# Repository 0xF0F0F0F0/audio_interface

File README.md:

# WM8731 audio_interface

KiCad project files for a stereo audio interface running at 24-bits/96kHz using the WM8731 codec.

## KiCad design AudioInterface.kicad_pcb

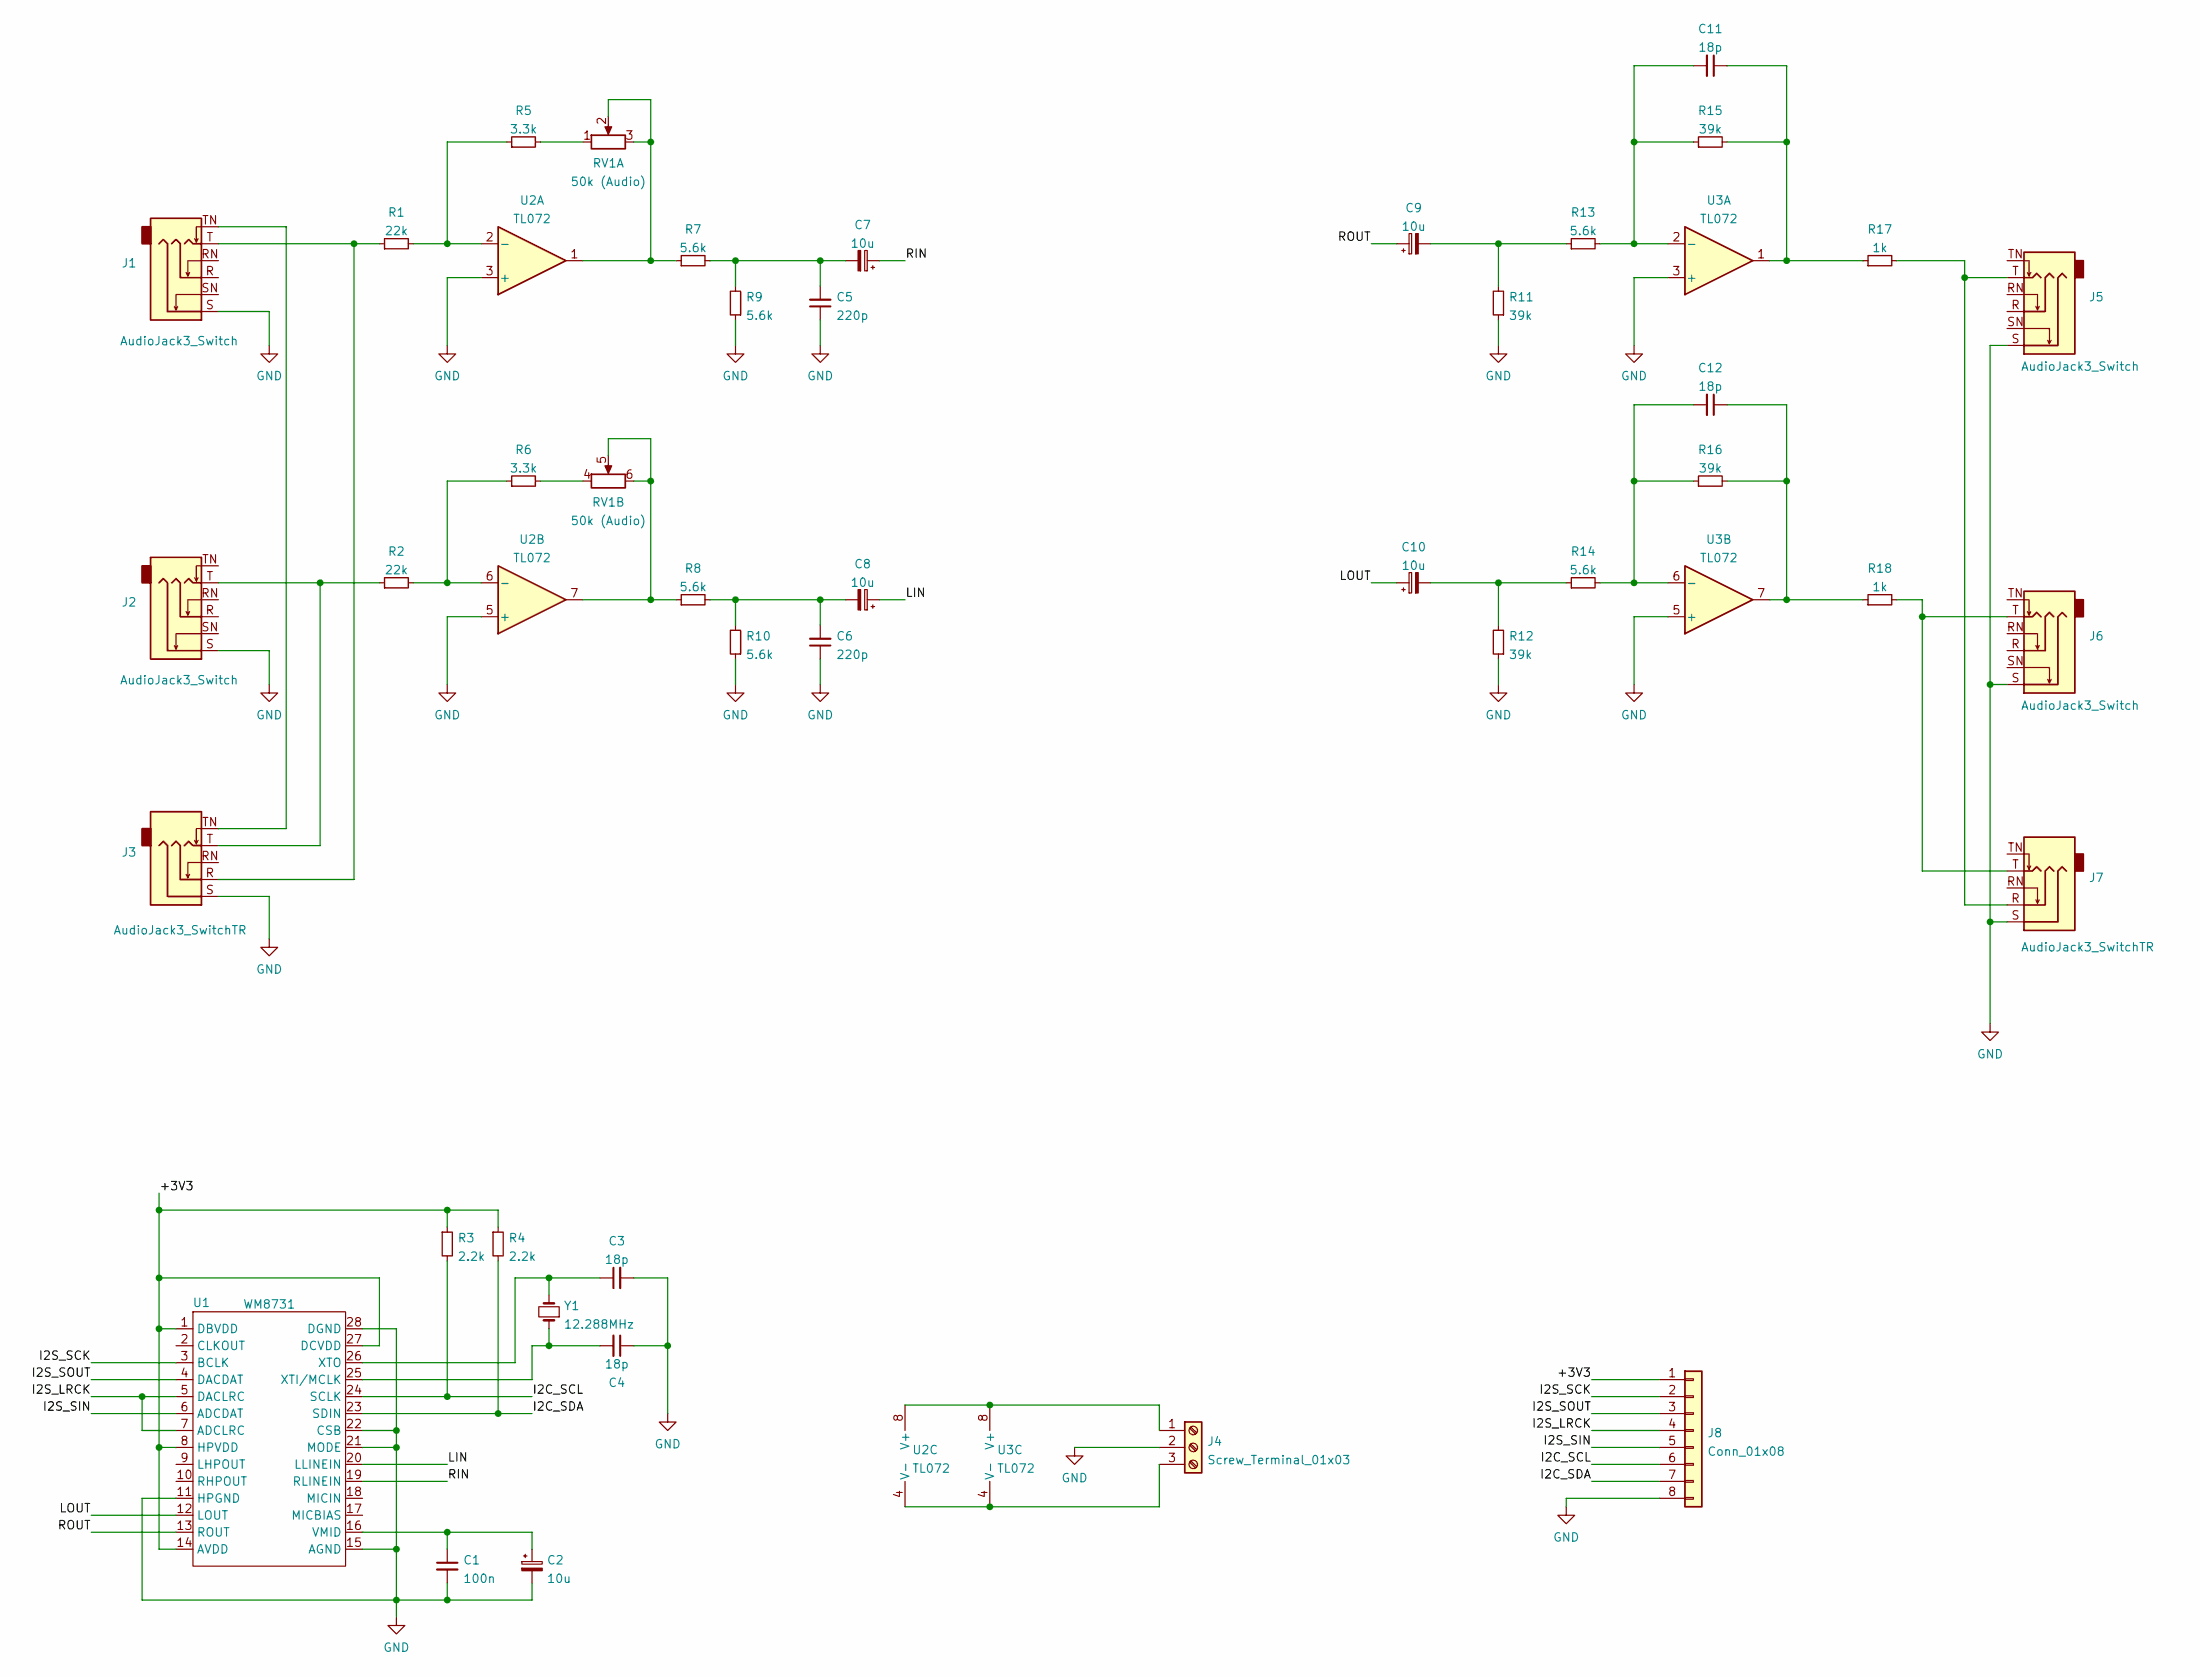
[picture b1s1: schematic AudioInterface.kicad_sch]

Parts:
C1: 100n; C_Rect_L7.2mm_W2.5mm_P5.00mm_FKS2_FKP2_MKS2_MKP2
C2, C7, C8, C9, C10: 10u; CP_Radial_D4.0mm_P1.50mm
C3, C4, C11, C12: 18p; C_Disc_D3.0mm_W1.6mm_P2.50mm
C5, C6: 220p; C_Disc_D3.0mm_W1.6mm_P2.50mm
J1, J2, J5, J6: AudioJack3_Switch; NMJ6HFD2
J3, J7: AudioJack3_SwitchTR; SJ1-3525N
J4: Screw_Terminal_01x03; 1-2834017-3-terminalblock
J8: Conn_01x08; PinHeader_1x08_P2.54mm_Vertical
R1, R2: 22k; R_0805_2012Metric_Pad1.15x1.40mm_HandSolder
R3, R4: 2.2k; R_0805_2012Metric_Pad1.15x1.40mm_HandSolder
R5, R6: 3.3k; R_0805_2012Metric_Pad1.15x1.40mm_HandSolder
R7, R8, R9, R10, R13, R14: 5.6k; R_0805_2012Metric_Pad1.15x1.40mm_HandSolder
R11, R12, R15, R16: 39k; R_0805_2012Metric_Pad1.15x1.40mm_HandSolder
R17, R18: 1k; R_0805_2012Metric_Pad1.15x1.40mm_HandSolder
RV1: 50k (Audio); PTV112-4
U1: WM8731; SSOP-28_5.3x10.2mm_P0.65mm
U2, U3: TL072; SOT-23-8_Handsoldering
Y1: 12.288MHz; Crystal_HC18-U_Vertical

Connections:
/+3V3: J8.1, R3.1, R4.1, U1.1 (DBVDD), U1.8 (HPVDD), U1.14 (AVDD), U1.27 (DCVDD)
/I2C_SCL: J8.6, R3.2, U1.24 (SCLK)
/I2C_SDA: J8.7, R4.2, U1.23 (SDIN)
/I2S_LRCK: J8.4, U1.5 (DACLRC), U1.7 (ADCLRC)
/I2S_SCK: J8.2, U1.3 (BCLK)
/I2S_SIN: J8.5, U1.6 (ADCDAT)
/I2S_SOUT: J8.3, U1.4 (DACDAT)
/LIN: C8.1, U1.20 (LLINEIN)
/LOUT: C10.1, U1.12 (LOUT)
/RIN: C7.1, U1.19 (RLINEIN)
/ROUT: C9.1, U1.13 (ROUT)
GND: C1.2, C2.2, C3.2, C4.1, C5.1, C6.1, J1.S, J2.S, J3.S, J4.2, J5.S, J6.S, J7.S, J8.8, R9.1, R10.1, R11.1, R12.1, U1.11 (HPGND), U1.15 (AGND), U1.21 (MODE), U1.22 (CSB), U1.28 (DGND), U2.3 (+), U2.5 (+), U3.3 (+), U3.5 (+)
unnamed: C1.1, C2.1, U1.16 (VMID)
unnamed: C3.1, U1.26 (XTO), Y1.2
unnamed: C4.2, U1.25 (XTI/MCLK), Y1.1
unnamed: C5.2, C7.2, R7.2, R9.2
unnamed: C6.2, C8.2, R8.2, R10.2
unnamed: C9.2, R11.2, R13.1
unnamed: C10.2, R12.2, R14.1
unnamed: C11.1, R15.2, R17.1, U3.1
unnamed: C11.2, R13.2, R15.1, U3.2 (-)
unnamed: C12.1, R16.2, R18.1, U3.7
unnamed: C12.2, R14.2, R16.1, U3.6 (-)
unnamed: J1.T, J3.R, R1.1
unnamed: J1.TN, J3.TN
unnamed: J2.T, J3.T, R2.1
unnamed: J4.1, U2.8 (V+), U3.8 (V+)
unnamed: J4.3, U2.4 (V-), U3.4 (V-)
unnamed: J5.T, J7.R, R17.2
unnamed: J6.T, J7.T, R18.2
unnamed: R1.2, R5.1, U2.2 (-)
unnamed: R2.2, R6.1, U2.6 (-)
unnamed: R5.2, RV1.1
unnamed: R6.2, RV1.4
unnamed: R7.1, RV1.2, RV1.3, U2.1
unnamed: R8.1, RV1.5, RV1.6, U2.7

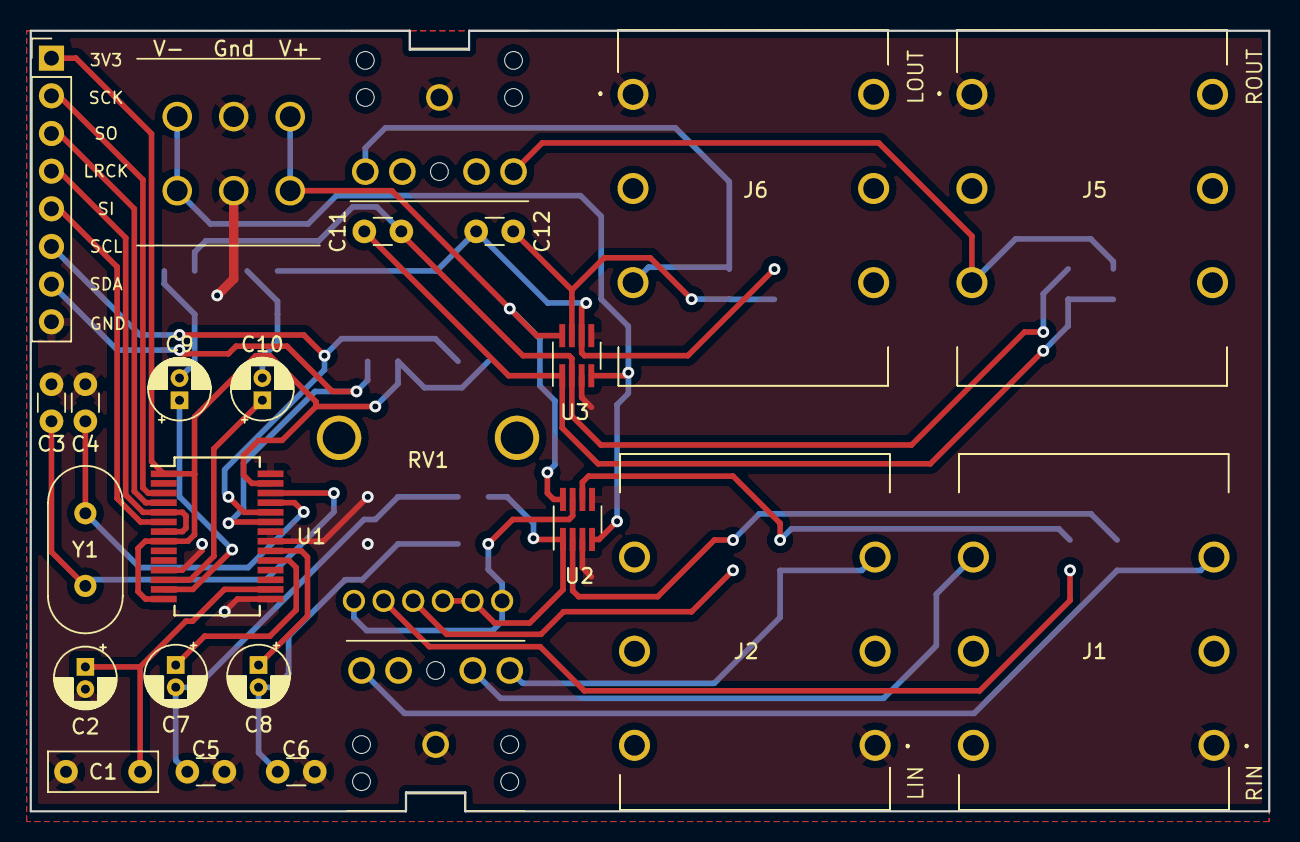
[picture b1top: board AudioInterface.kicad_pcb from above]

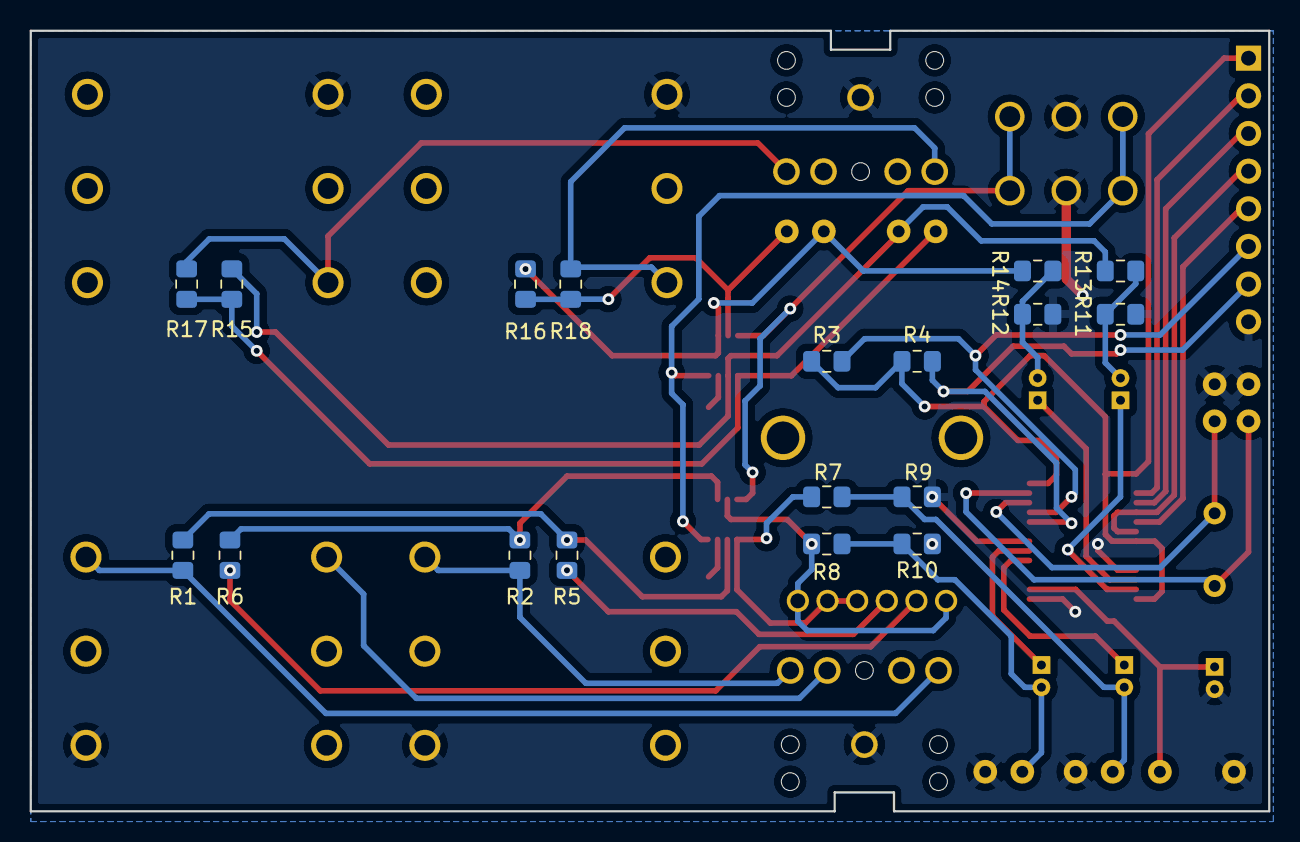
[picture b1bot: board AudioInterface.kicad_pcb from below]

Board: 2 copper layers, 83.5 x 52.7 mm, 43 parts (18 on the bottom side), 36 nets.
